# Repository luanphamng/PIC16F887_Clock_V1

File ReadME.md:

# @pml1hc's PIC16F887 RTC Project

This repository contains my PIC16F887 RTC Project
Firmware is developed in MPLABX v3.61
Schematic and PCB is developed by KiCAD

## Schematic Symbols

## PCB Footprints

## Licence

All content licensed under the PML1HClicence.

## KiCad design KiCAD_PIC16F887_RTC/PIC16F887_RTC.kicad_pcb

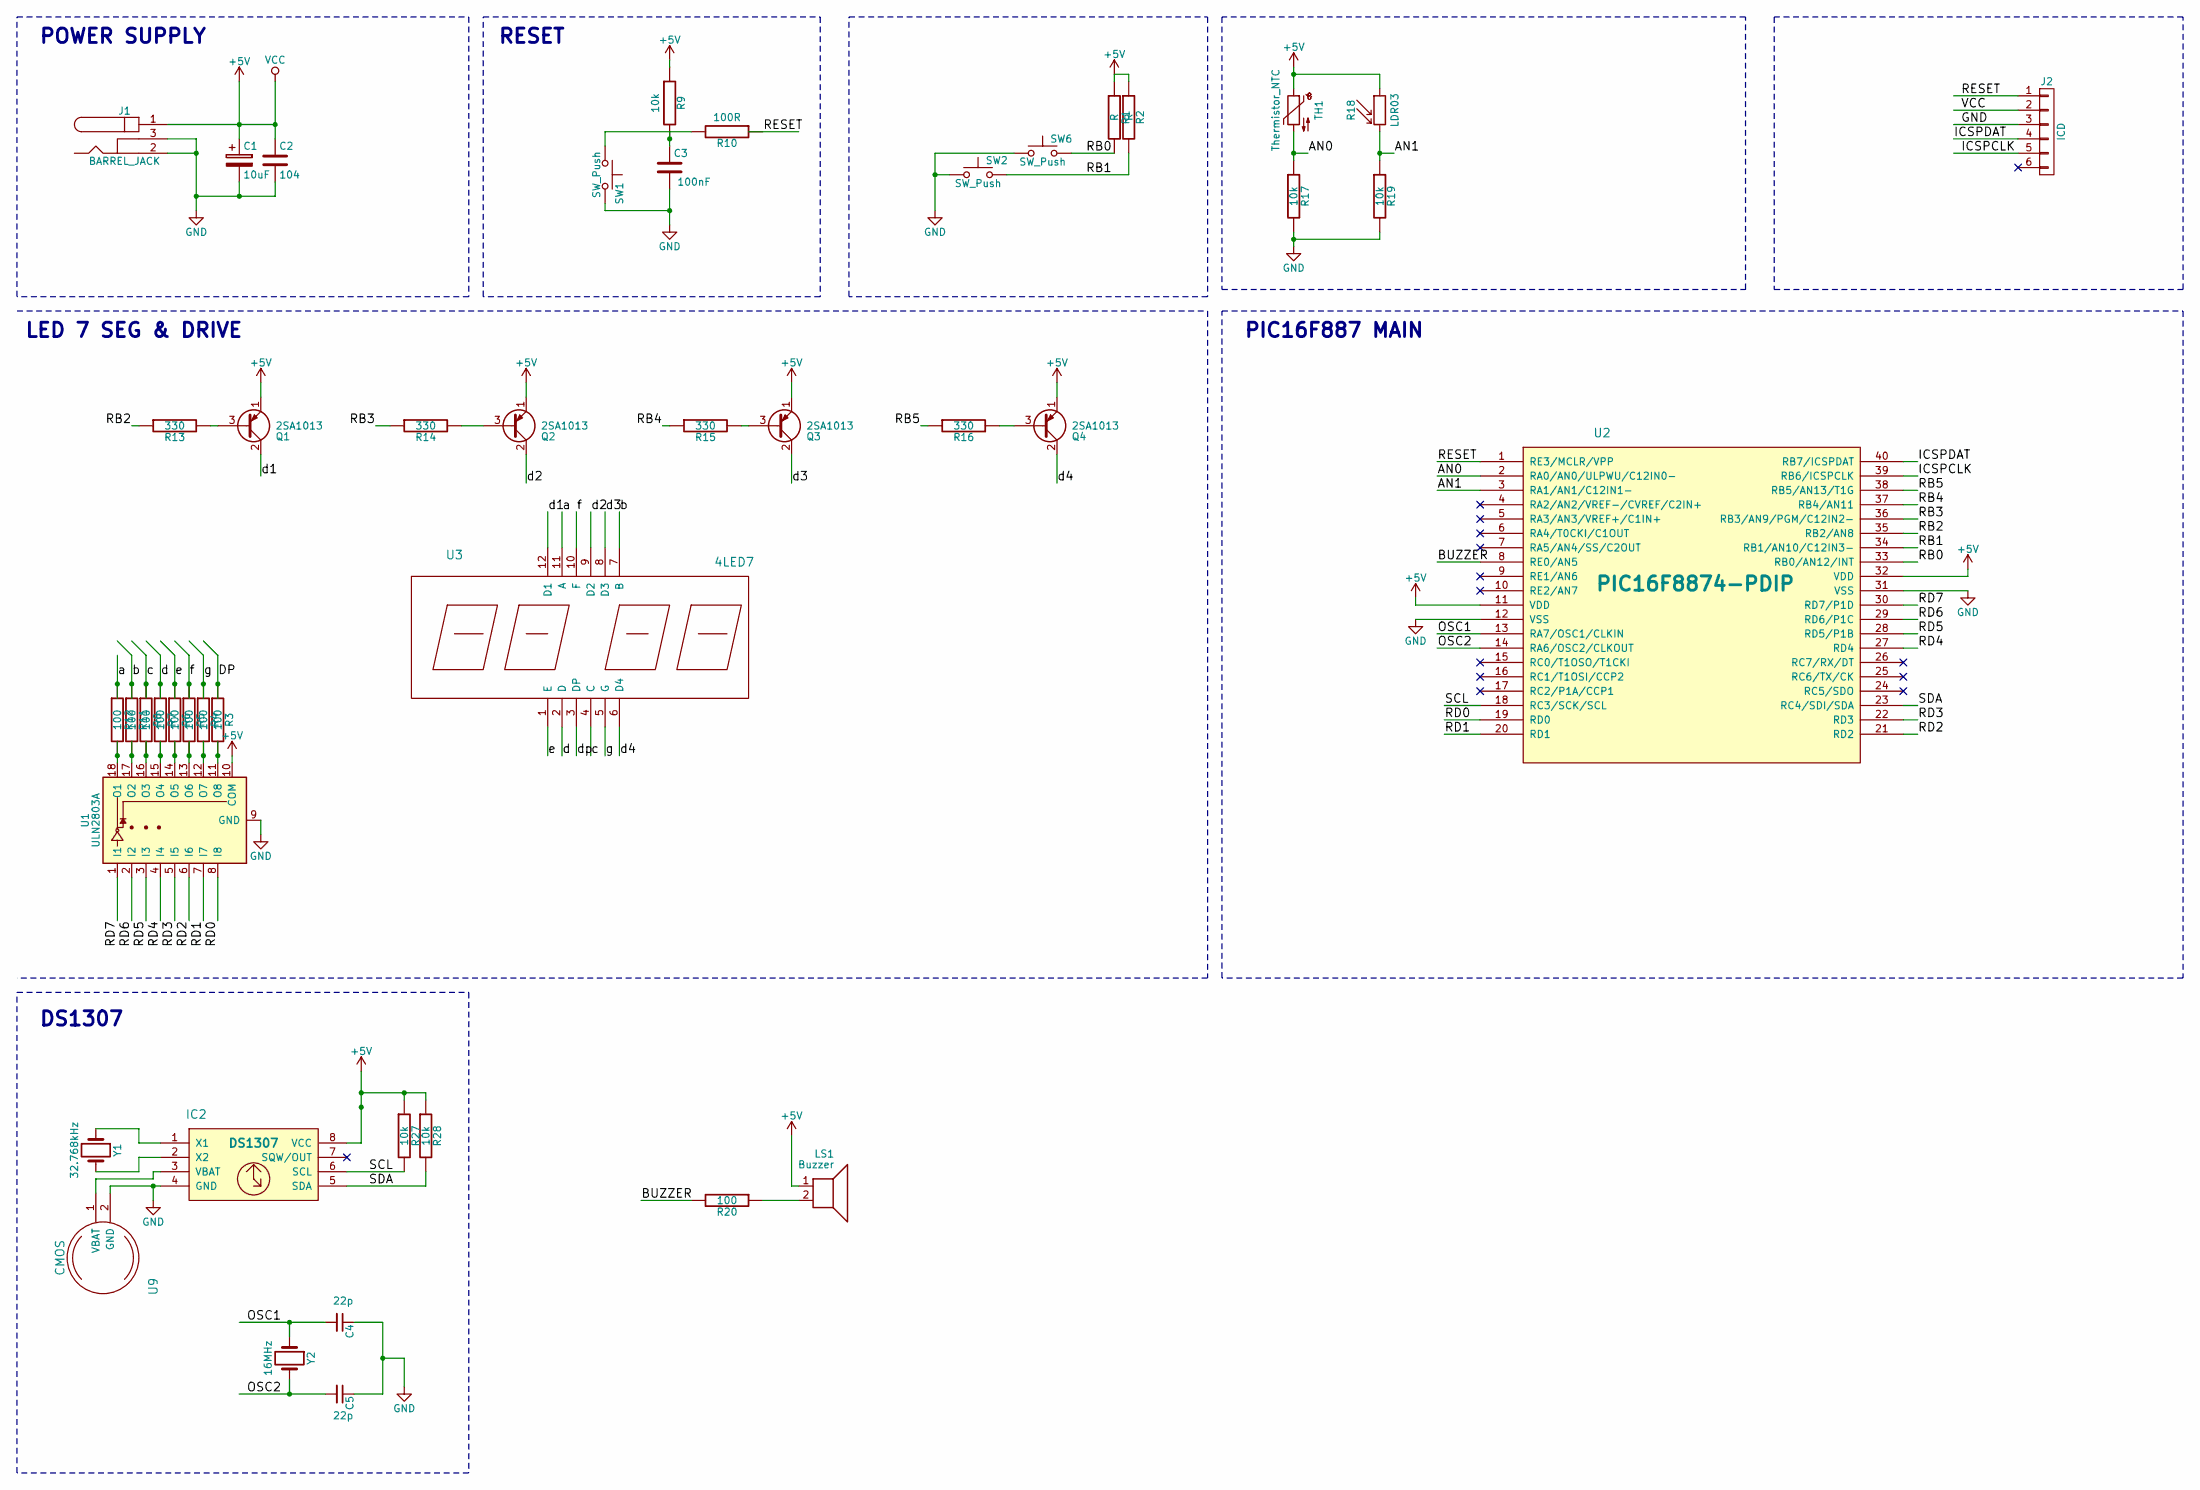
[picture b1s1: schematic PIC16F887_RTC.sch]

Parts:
C1: 10uF; CP_Radial_D8.0mm_P5.00mm
C2: 104; C_Disc_D3.0mm_W1.6mm_P2.50mm
C3: 100nF; C_Axial_L3.8mm_D2.6mm_P7.50mm_Horizontal
C4, C5: 22p; C_Axial_L3.8mm_D2.6mm_P7.50mm_Horizontal
IC2: DS1307; DIP-8_W7.62mm
J1: BARREL_JACK; POWER_JACK_PTH
J2: ICD; Pin_Header_Straight_1x06_Pitch2.54mm
LS1: Buzzer; MagneticBuzzer_ProSignal_ABI-009-RC
Q1, Q2, Q3, Q4: 2SA1013; TO-92_Molded_Narrow
R1, R2: R; R_Axial_DIN0309_L9.0mm_D3.2mm_P15.24mm_Horizontal
R3, R4, R5, R6, R7, R8, R11, R12, R20: 100; R_Axial_DIN0309_L9.0mm_D3.2mm_P15.24mm_Horizontal
R9, R17, R19, R27, R28: 10k; R_Axial_DIN0309_L9.0mm_D3.2mm_P15.24mm_Horizontal
R10: 100R; R_Axial_DIN0309_L9.0mm_D3.2mm_P15.24mm_Horizontal
R13, R14, R15, R16: 330; R_Axial_DIN0309_L9.0mm_D3.2mm_P15.24mm_Horizontal
R18: LDR03; Resistor_LDR_10x8.5_RM7.6
SW1, SW2, SW6: SW_Push; Pin_Header_Straight_1x02_Pitch2.54mm
TH1: Thermistor_NTC; C_Disc_D3.0mm_W1.6mm_P2.50mm
U1: ULN2803A; DIP-18_W7.62mm
U2: PIC16F8874-PDIP; DIP-40_W15.24mm
U3: 4LED7
U9: CMOS; CMOS CR2032
Y1: 32.768kHz; Crystal_C26-LF_d2.1mm_l6.5mm_Horizontal
Y2: 16MHz; CRYSTAL_HC49_PTH

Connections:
+5V: C1.1, C2.1, IC2.8 (VCC), J1.1, J2.2, LS1.1, Q1.1 (E), Q2.1 (E), Q3.1 (E), Q4.1 (E), R1.1, R2.1, R9.1, R18.1, R27.1, R28.1, TH1.1, U1.10 (COM), U2.11 (VDD), U2.32 (VDD)
/AN0: R17.1, TH1.2, U2.2 (RA0/AN0/ULPWU/C12IN0-)
/AN1: R18.2, R19.1, U2.3 (RA1/AN1/C12IN1-)
/BUZZER: R20.2, U2.8 (RE0/AN5)
/DP: R3.1, U3.3 (DP)
/ICSPCLK: J2.5, U2.39 (RB6/ICSPCLK)
/ICSPDAT: J2.4, U2.40 (RB7/ICSPDAT)
/OSC1: C4.2, U2.13 (RA7/OSC1/CLKIN), Y2.1
/OSC2: C5.2, U2.14 (RA6/OSC2/CLKOUT), Y2.2
/RB0: R1.2, SW6.2, U2.33 (RB0/AN12/INT)
/RB1: R2.2, SW2.2, U2.34 (RB1/AN10/C12IN3-)
/RB2: R13.1, U2.35 (RB2/AN8)
/RB3: R14.1, U2.36 (RB3/AN9/PGM/C12IN2-)
/RB4: R15.1, U2.37 (RB4/AN11)
/RB5: R16.1, U2.38 (RB5/AN13/T1G)
/RD0: U1.8 (I8), U2.19 (RD0)
/RD1: U1.7 (I7), U2.20 (RD1)
/RD2: U1.6 (I6), U2.21 (RD2)
/RD3: U1.5 (I5), U2.22 (RD3)
/RD4: U1.4 (I4), U2.27 (RD4)
/RD5: U1.3 (I3), U2.28 (RD5/P1B)
/RD6: U1.2 (I2), U2.29 (RD6/P1C)
/RD7: U1.1 (I1), U2.30 (RD7/P1D)
/RESET: J2.1, R10.1, U2.1 (RE3/MCLR/VPP)
/SCL: IC2.6 (SCL), R27.2, U2.18 (RC3/SCK/SCL)
/SDA: IC2.5 (SDA), R28.2, U2.23 (RC4/SDI/SDA)
/a: R12.1, U3.11 (A)
/b: R11.1, U3.7 (B)
/c: R8.1, U3.4 (C)
/d: R7.1, U3.2 (D)
/d1: Q1.2 (C), U3.12 (D1)
/d2: Q2.2 (C), U3.9 (D2)
/d3: Q3.2 (C), U3.8 (D3)
/d4: Q4.2 (C), U3.6 (D4)
/e: R6.1, U3.1 (E)
/f: R5.1, U3.10 (F)
/g: R4.1, U3.5 (G)
GND: C1.2, C2.2, C3.2, C4.1, C5.1, IC2.4 (GND), J1.2, J1.3, J2.3, R17.2, R19.2, SW1.2, SW2.1, SW6.1, U1.9 (GND), U2.12 (VSS), U2.31 (VSS), U9.2 (GND)
unnamed: C3.1, R9.2
unnamed: IC2.1 (X1), Y1.1
unnamed: IC2.2 (X2), Y1.2
unnamed: IC2.3 (VBAT), U9.1 (VBAT)
unnamed: LS1.2, R20.1
unnamed: Q1.3 (B), R13.2
unnamed: Q2.3 (B), R14.2
unnamed: Q3.3 (B), R15.2
unnamed: Q4.3 (B), R16.2
unnamed: R3.2, U1.11 (O8)
unnamed: R4.2, U1.12 (O7)
unnamed: R5.2, U1.13 (O6)
unnamed: R6.2, U1.14 (O5)
unnamed: R7.2, U1.15 (O4)
unnamed: R8.2, U1.16 (O3)
unnamed: R10.2, SW1.1
unnamed: R11.2, U1.17 (O2)
unnamed: R12.2, U1.18 (O1)

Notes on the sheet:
RESET
LED 7 SEG & DRIVE
PIC16F887 MAIN
DS1307
POWER SUPPLY

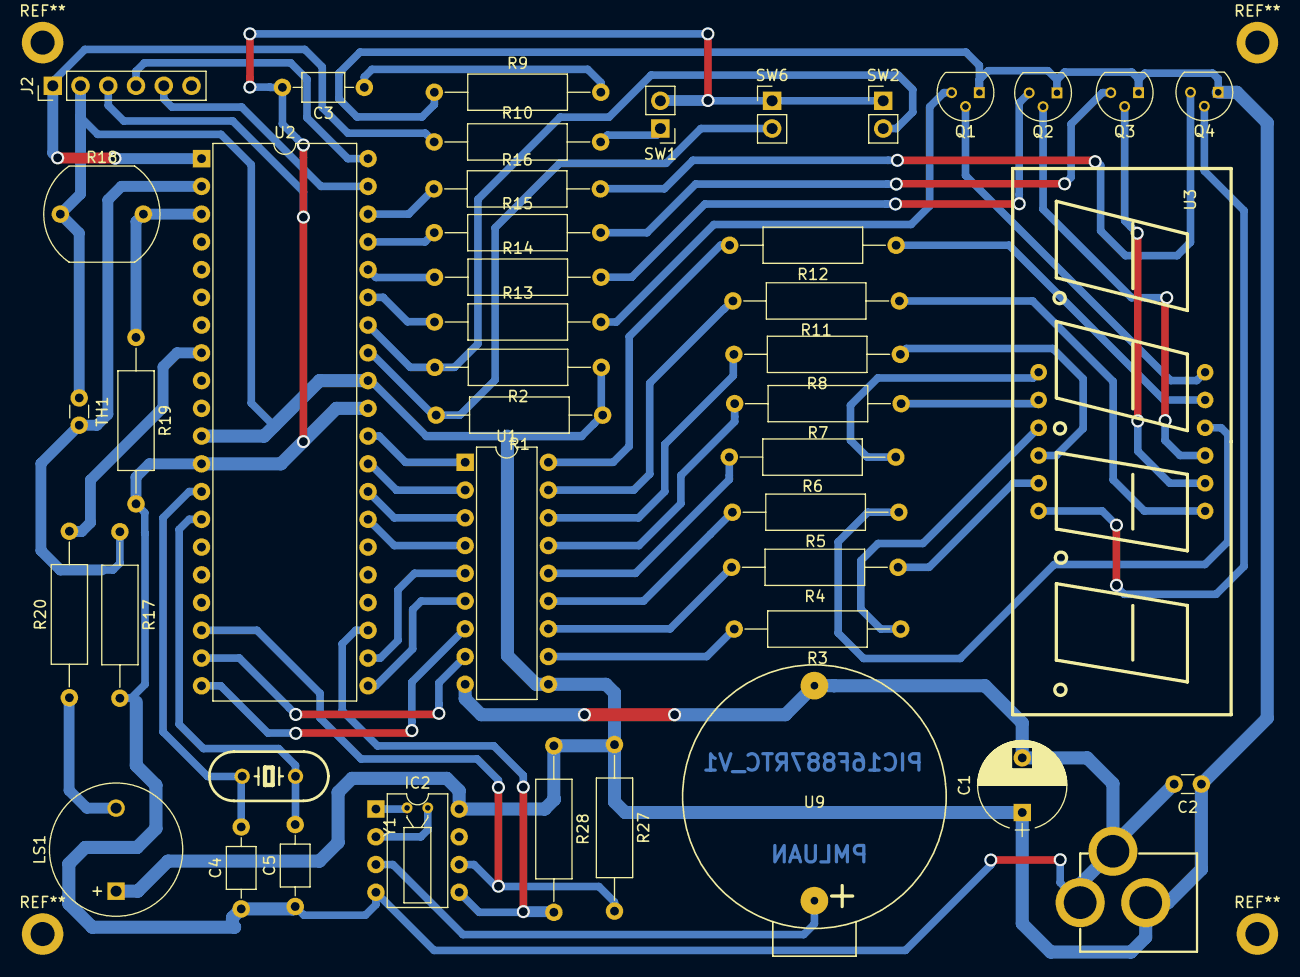
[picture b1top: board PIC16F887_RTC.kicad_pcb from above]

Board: 2 copper layers, 45 parts (0 on the bottom side), 56 nets.

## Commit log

2017-08-25 Initial Commint
2017-08-25 Copper pour done
2017-08-26 Add mounting hole done - No DRC
2017-08-26 Added 4 mounting hole - No DRC
2017-09-09 Test Circuit done, display Minute and sec
2017-09-10 test mode
2017-09-17 Error Modifiy Clock
